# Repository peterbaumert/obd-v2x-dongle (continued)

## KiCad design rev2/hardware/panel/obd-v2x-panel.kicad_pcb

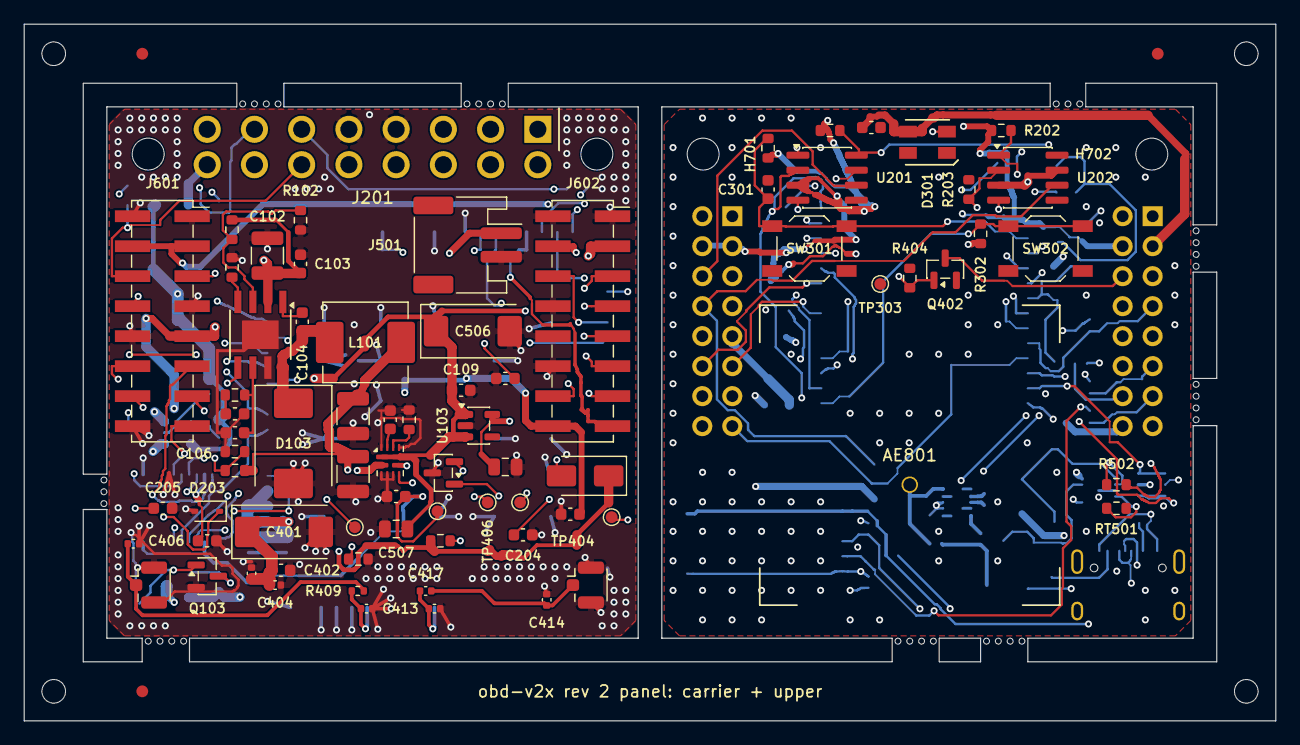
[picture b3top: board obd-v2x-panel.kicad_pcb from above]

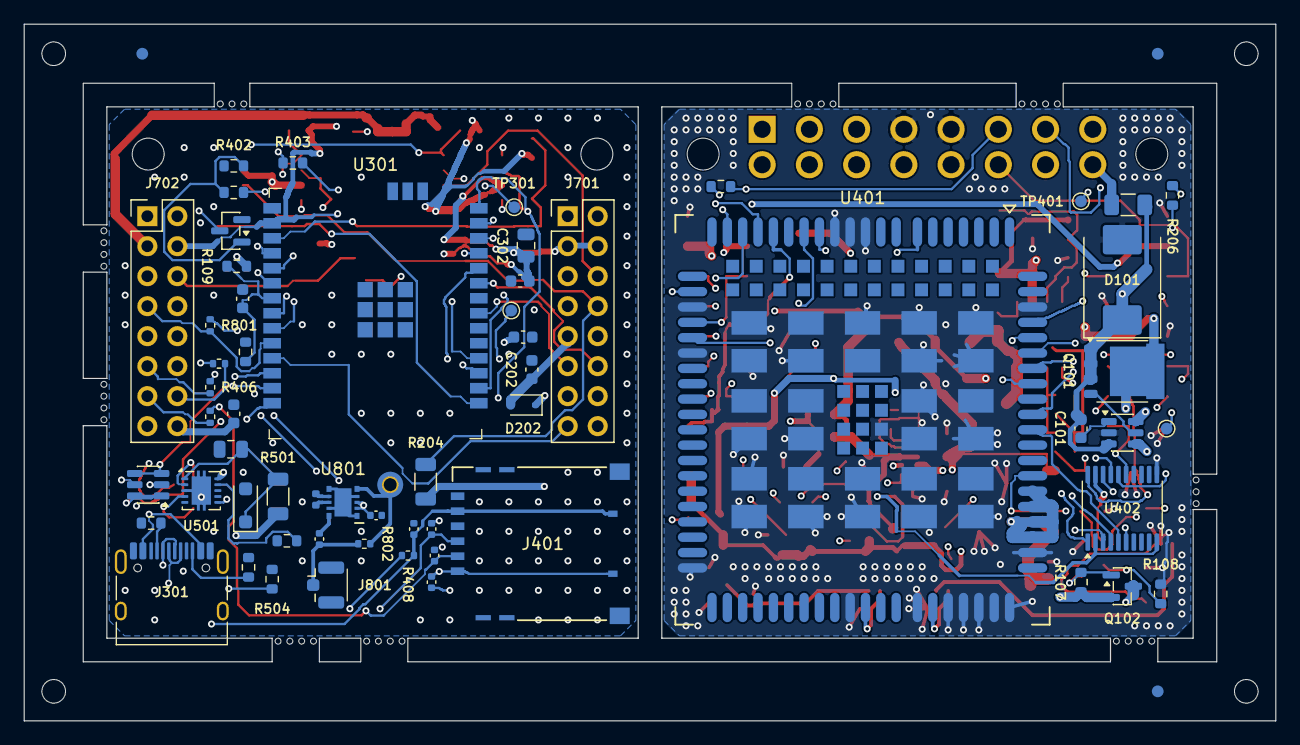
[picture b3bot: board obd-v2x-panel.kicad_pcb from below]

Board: 4 copper layers, 106.0 x 59.0 mm, 182 parts (62 on the bottom side), 112 nets.

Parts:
AE801: CGGBP.25.4.A.02; Antenna_Taoglas_CGGBP.25.4.A.02
C101, C104, C111, C201, C303, C304, C402, C405, C406: 100nF; C_0603_1608Metric
C102: 10uF 50V; C_1210_3225Metric
C103, C202: 100nF 50V; C_0603_1608Metric
C105: 5.6nF; C_0603_1608Metric
C106: 47pF; C_0603_1608Metric
C107, C108: 47uF 10V; C_1210_3225Metric
C109, C301, C502, C505: 1uF; C_0603_1608Metric
C110, C302, C507: 10uF; C_0805_2012Metric
C203: 220pF 50V; C_0603_1608Metric
C204, C205: 560pF 50V; C_0603_1608Metric
C401: 220uF 6.3V; CP_EIA-7343-20_Kemet-V
C403, C407, C408, C409, C417, C801: 33pF; C_0402_1005Metric
C404: 10pF; C_0402_1005Metric
C410, C802: 100nF; C_0402_1005Metric
C411, C412, C413, C414: DNP; C_0402_1005Metric
C501: 1uF 50V; C_0805_2012Metric
C504: 10nF; C_0603_1608Metric
C506: 220uF; CP_EIA-7343-31_Kemet-D
D101: SMCJ33CA; D_SMC
D102: SS14; D_SMA
D103: B560C; D_SMC
D201: NUP2105L; SOT-23
D202: B0540WS; D_SOD-323
D203: PESD1LIN; D_SOD-323
D301: SK6812MINI-HS; LED_SK6812MINI-HS_3.7x3.5mm
D501: SMF24A; D_SOD-123F
F101: 2A slow; Fuse_1206_3216Metric
FID1, FID2, FID3, FID4, FID5, FID6: (no value)
H601, H602, H701, H702: M2.5; MountingHole_2.7mm_M2.5
J201: OBD2_J1962_Plug; OBD2_J1962_Plug_PCB
J301: USB-C; USB_C_Receptacle_HRO_TYPE-C-31-M-12
J401: Micro-SIM; microSIM_Molex_78646-3001
J402: U.FL LTE main; U.FL_Hirose_U.FL-R-SMT-1_Vertical
J403: U.FL GNSS; U.FL_Hirose_U.FL-R-SMT-1_Vertical
J501: Battery 1S; JST_PH_S2B-PH-SM4-TB_1x02-1MP_P2.00mm_Horizontal
J601, J602: Socket 2x8; PinSocket_2x08_P2.54mm_Vertical_SMD
J701, J702: Header 2x8; PinHeader_2x08_P2.54mm_Vertical
J801: U.FL to carrier J403; U.FL_Hirose_U.FL-R-SMT-1_Vertical
L101: 6.8uH 4.5A; L_Sunlord_MWSA0605S
L801: 9.1nH; L_0402_1005Metric
MB1, MB2, MB3, MB4, MB5, MB6, MB7, MB8, MB9, MB10, MB11, MB12, MB13, MB14, MB15, MB16, MB17, MB18, MB19, MB20, MB21, MB22, MB23, MB24, MB25, MB26, MB27, MB28, MB29, MB30, MB31, MB32, MB33, MB34: (no value)
Q101: PSMN7R0-60YS; LFPAK56
Q102: AO3401A; SOT-23
Q103: 2N7002; SOT-23
Q401, Q402: MMBT3904; SOT-23
R101: 470k; R_0603_1608Metric
R102: 120k; R_0603_1608Metric
R103: 162k; R_0603_1608Metric
R104: 37.4k; R_0603_1608Metric
R105, R110, R201, R301, R302: 10k; R_0603_1608Metric
R106: 12k; R_0603_1608Metric
R107, R108, R109, R203: 100k; R_0603_1608Metric
R202, R401, R403: 4.7k; R_0603_1608Metric
R204: 510 0.5W; R_1206_3216Metric
R205, R206: 100R; R_0603_1608Metric
R303, R304: 5.1k; R_0603_1608Metric
R402, R404: 47k; R_0603_1608Metric
R405, R406, R407: 22R; R_0402_1005Metric
R408: 15k; R_0402_1005Metric
R409, R802: 0R; R_0402_1005Metric
R501: 33R 0.5W; R_1206_3216Metric
R502: 4.3k; R_0603_1608Metric
R503: 24k 1%; R_0603_1608Metric
R504, R505: 82k 1%; R_0603_1608Metric
R506: 10k 1%; R_0603_1608Metric
R507: 30.1k 1%; R_0603_1608Metric
R801: 100R; R_0402_1005Metric
RT501: 10k NTC; R_0603_1608Metric
SW301: RESET; SW_SPST_TL3342
SW302: BOOT; SW_SPST_TL3342
TH1, TH2, TH3, TH4: (no value)
TP301: UART0_TX; TestPoint_Pad_D1.0mm
TP302: IO12; TestPoint_Pad_D1.0mm
TP303: GND; TestPoint_Pad_D1.0mm
TP401: LTE_USB_VBUS; TestPoint_Pad_D1.0mm
TP402: LTE_USB_DP; TestPoint_Pad_D1.0mm
TP403: LTE_USB_DM; TestPoint_Pad_D1.0mm
TP404: LTE_USB_BOOT; TestPoint_Pad_D1.0mm
TP405: LTE_DBG_TXD; TestPoint_Pad_D1.0mm
TP406: LTE_DBG_RXD; TestPoint_Pad_D1.0mm
TP407: LTE_1V8; TestPoint_Pad_D1.0mm
U101: LM74700-Q1; SOT-23-6
U102: TPS54360DDA; TI_SO-PowerPAD-8
U103: TLV75733PDBV; SOT-23-5
U201: TCAN334; SOIC-8_3.9x4.9mm_P1.27mm
U202: TJA1021T/20; SOIC-8_3.9x4.9mm_P1.27mm
U301: ESP32-C5-WROOM-1U-N16R8; ESP32-C5-WROOM-1U
U302: USBLC6-2SC6; SOT-23-6
U401: EC200U-EU; Quectel_EC200U
U402: TXS0108EPW; TSSOP-20_4.4x6.5mm_P0.65mm
U501: BQ25171-Q1; Texas_DRC0010J
U502: TPS2121; Texas_VQFN-HR-12_2x2.5mm_P0.5mm
U801: SKY65943-11; Skyworks_SKY65943-11_MCM-10_2.5x2.5mm

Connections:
+3V3: C110.1, C406.1, J601.3, J601.4, J602.4, U103.5, U402.19
/LTE + GNSS (EC200U)/LTE_ANT_GNSS: C413.1, C417.1, U401.47
/LTE + GNSS (EC200U)/LTE_ANT_GNSS_UFL: C414.1, C417.2, J403.1
/LTE + GNSS (EC200U)/LTE_ANT_MAIN: C411.1, R409.1, U401.49
/LTE + GNSS (EC200U)/LTE_CTS_1V8: U401.64, U402.5
/LTE + GNSS (EC200U)/LTE_DBG_RXD: TP406.1, U401.11
/LTE + GNSS (EC200U)/LTE_DBG_TXD: TP405.1, U401.12
/LTE + GNSS (EC200U)/LTE_RTS_1V8: U401.65, U402.4
/LTE + GNSS (EC200U)/LTE_RXD_1V8: U401.68, U402.1
/LTE + GNSS (EC200U)/LTE_STATUS: U401.61, U402.6
/LTE + GNSS (EC200U)/LTE_TXD_1V8: U401.67, U402.3
/LTE + GNSS (EC200U)/LTE_USB_BOOT: TP404.1, U401.115
/LTE + GNSS (EC200U)/LTE_USB_DM: TP403.1, U401.70
/LTE + GNSS (EC200U)/LTE_USB_DP: TP402.1, U401.69
/LTE + GNSS (EC200U)/LTE_USB_VBUS: TP401.1, U401.71
/Power/BUCK_COMP: C106.1, R106.1, U102.6
/Power/BUCK_EN: R101.2, R102.1, U102.3
/Power/BUCK_FB: R104.2, R105.1, U102.5
/Power/LTE_PWR_ON_N: Q102.1, Q103.3, R107.2
/Power/VBAT_F: C101.2, D101.1, F101.2, Q101.1, Q101.2, Q101.3, U101.3, U101.6
CANH: D201.1, J201.6, J601.5, R205.1
CANL: D201.2, J201.14, J601.6, R206.1
GND: C102.2, C103.2, C105.2, C106.2, C107.2, C108.2, C109.2, C110.2, C203.2, C204.2, C205.2, C401.2, C402.2, C403.2, C404.2, C405.2, C406.2, C411.2, C412.2, C413.2, C414.2, C504.2, C505.2, C506.2, C507.2, D101.2, D103.2, D201.3, D203.2, J201.4, J201.5, J402.2, J403.2, J501.2, J601.1, J601.2, J601.7, J601.10, J601.16, J602.1, J602.2, J602.8, J602.10, J602.12, Q103.2, R102.2, R103.2, R105.2, R108.2, R506.2, R507.2, U101.2, U102.7, U102.9, U103.2, U401.8, U401.9, U401.10, U401.19, U401.22, U401.36, U401.46, U401.48, U401.50, U401.51, U401.52, U401.53, U401.54, U401.56, U401.72, U401.76, U401.85, U401.86, U401.87, U401.88, U401.89, U401.90, U401.91, U401.92, U401.93, U401.94, U401.95, U401.96, U401.97, U401.98, U401.99, U401.100, U401.101, U401.102, U401.103, U401.104, U401.105, U401.106, U401.107, U401.108, U401.109, U401.110, U401.111, U401.112, U402.11, U502.3, U502.4, U502.5, U502.9, U502.12
K_LINE: C203.1, D203.1, J201.7, J601.8
LTE_1V8: C405.1, TP407.1, U401.7, U402.2, U402.10
LTE_PWRKEY: J602.5, U401.21
LTE_PWR_EN: J602.7, Q103.1, R108.1
LTE_RESET_N: J602.6, U401.20
LTE_STATUS_3V3: J601.15, U402.15
LTE_USIM_CLK: J602.11, U401.16
LTE_USIM_DATA: J602.13, U401.15
LTE_USIM_RST: J602.14, U401.17
MCU_CTS_LTE: J601.14, U402.16
MCU_RTS_LTE: J601.13, U402.17
MCU_RX_LTE: J601.12, U402.18
MCU_TX_LTE: J601.11, U402.20
unnamed: C105.1, R106.2
unnamed: C204.1, R205.2
unnamed: C205.1, R206.2
unnamed: C104.2, D103.1, L101.1, U102.8
unnamed: C412.1, J402.1, R409.2
unnamed: Q101.4, U101.5
unnamed: C101.1, U101.1
unnamed: C104.1, U102.1
unnamed: R103.1, U102.4
unnamed: R507.1, U502.10
unnamed: R505.2, R506.1, U502.6
unnamed: C504.1, U502.11
OBD_VBAT: F101.1, J201.16
SIM_VDD: J602.15, U401.14
U.+3V3: C201.1, C302.1, C303.1, J701.3, J701.4, J702.4, R201.1, R202.1, R301.1, R302.1, U201.3, U301.2
U./GNSS patch + front end/GNSS_VCC: C802.1, R801.2, U801.2, U801.3
U./MCU (ESP32-C5, USB)/ESP_BOOT: R302.2, SW302.1, U301.15
U./MCU (ESP32-C5, USB)/IO12: TP302.1, U301.24
U./MCU (ESP32-C5, USB)/LED_DIN: D301.2, U301.18
U./MCU (ESP32-C5, USB)/UART0_TX: TP301.1, U301.25
U./MCU (ESP32-C5, USB)/USB_DN: J301.A7, J301.B7, U301.13, U302.3, U302.4
U./MCU (ESP32-C5, USB)/USB_DP: J301.A6, J301.B6, U301.14, U302.1, U302.6
U./Micro-SIM/SIM_CLK: C408.1, J401.3, R406.2
U./Micro-SIM/SIM_IO: C407.1, J401.7, R405.2
U./Micro-SIM/SIM_RST: C409.1, J401.2, R407.2
U.CANH: J701.5, U201.7
U.CANL: J701.6, U201.6
U.CAN_RX: U201.4, U301.16
U.CAN_STB: R201.2, U201.8, U301.12
U.CAN_TX: U201.1, U301.17
U.GND: C111.2, C201.2, C202.2, C301.2, C302.2, C303.2, C304.2, C407.2, C408.2, C409.2, C410.2, C501.2, C502.2, C802.2, D301.1, D501.2, J301.A1, J301.A12, J301.B1, J301.B12, J301.SH, J401.5, J401.SH, J701.1, J701.2, J701.7, J701.10, J701.16, J702.1, J702.2, J702.8, J702.10, J702.12, J801.2, Q401.2, Q402.2, R110.2, R203.2, R303.2, R304.2, R402.2, R404.2, R502.2, R503.2, R504.2, RT501.2, SW301.2, SW302.2, TP303.1, U201.2, U201.5, U202.5, U301.1, U301.28, U301.29, U301.30, U301.32, U302.2, U501.3, U501.5, U501.11, U801.1, U801.4, U801.6, U801.9, U801.11
U.KL_RX: R202.2, U202.1, U301.6
U.KL_SLP_N: R203.1, U202.2, U301.9
U.KL_TX: U202.4, U301.8
U.K_LINE: J701.8, R204.2, U202.6
U.LTE_PWRKEY: J702.5, Q401.3
U.LTE_PWRKEY_CTL: R401.1, U301.4
U.LTE_PWR_EN: J702.7, R801.1, U301.10
U.LTE_RESET_CTL: R403.1, U301.5
U.LTE_RESET_N: J702.6, Q402.3
U.LTE_STATUS_3V3: J701.15, U301.11
U.LTE_USIM_CLK: J702.11, R406.1
U.LTE_USIM_DATA: J702.13, R405.1, R408.2
U.LTE_USIM_RST: J702.14, R407.1
U.MCU_CTS_LTE: J701.14, U301.26
U.MCU_RTS_LTE: J701.13, U301.27
U.MCU_RX_LTE: J701.12, U301.23
U.MCU_TX_LTE: J701.11, U301.21
U.Net-(AE801-A): AE801.1, R802.1, U801.5
U.Net-(D202-K): D202.1, R204.1
U.Net-(D501-K): C501.1, D501.1, R501.2, U501.1
U.Net-(J301-CC1): J301.A5, R303.1
U.Net-(J301-CC2): J301.B5, R304.1
U.Net-(J801-In): C801.2, J801.1, R802.2
U.Net-(Q401-B): Q401.1, R401.2, R402.1
U.Net-(Q402-B): Q402.1, R403.2, R404.1
U.Net-(U301-EN): C301.1, R301.2, SW301.1, U301.3
U.Net-(U501-CHM_TMR): R504.1, U501.6
U.Net-(U501-ISET): R502.1, U501.2
U.Net-(U501-TS): RT501.1, U501.4
U.Net-(U501-VSET): R503.1, U501.9
U.Net-(U801-AMP_IN): L801.2, U801.8
U.Net-(U801-FILT_OUT): L801.1, U801.7
U.Net-(U801-RF_OUT): C801.1, U801.10
U.SIM_VDD: C410.1, J401.1, J702.15, R408.1
U.VBUS_USB: J301.A4, J301.A9, J301.B4, J301.B9, J702.9, U302.5
U.VCELL: C502.1, J702.16, U501.10
U.VIN_PROT: C202.1, D202.2, J701.9, R109.1, R501.1, U202.3, U202.7
U.VSENSE: C111.1, R109.2, R110.1, U301.7
U.VSYS_3V8: C304.1, D301.3, J702.3
VBAT_LTE: C401.1, C402.1, C403.1, C404.1, Q102.3, U401.57, U401.58, U401.59, U401.60
VBUCK_3V8: C107.1, C108.1, L101.2, R104.1, U502.7
VBUS_USB: D102.2, J602.9
VCELL: C505.1, J501.1, J602.16, U502.2
VIN_PROT: C102.1, C103.1, D102.1, J601.9, Q101.5, R101.1, R505.1, U101.4, U102.2
VSYS_3V8: C109.1, C506.1, C507.1, J602.3, Q102.2, R107.1, U103.1, U103.3, U502.1, U502.8

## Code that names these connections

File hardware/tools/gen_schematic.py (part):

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
    sh.text('Input protection: fuse, TVS, ideal-diode reverse protection', g(5), g(6), 1.5, True)
    F = sh.part('Device:Fuse', 'F101', '2A slow', 'Fuse:Fuse_1206_3216Metric', g(14), y0, 90, fields=H(g(14), y0))
    sh.glabel('OBD_VBAT', F.out(1, 1), 'L', 'input')
    sh.w(F.out(1, 1), F[1])

    xt = g(19)
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    sh.w(C[1], U['VCAP'])
    sh.w(C[2], (xv, y0))
    sh.w(U['EN'], (xv - g(2), U['EN'][1]))
    sh.label('VBAT_F', (xv - g(2), U['EN'][1]), 'L')
    sh.label('VBAT_F', (xt + g(3), y0), 'R')
    # main line, input side
    sh.w(F[2], (xt, y0), (xt + g(3), y0), (xv, y0), (xa, y0), Q['S'])
    sh.rail('VIN_PROT', (xc + g(3), y0))
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    Dv.fields = {'ref': (xu + 2.54, Dv.y - 1.27, 'left'), 'val': (xu + 2.54, Dv.y + 1.27, 'left')}
    sh.w(Dv['K'], (xu, y0))
    sh.w(Dv['A'], (xu, Dv['A'][1] - g(1)), (xu - g(1), Dv['A'][1] - g(1)))
    sh.glabel('VBUS_USB', (xu - g(1), Dv['A'][1] - g(1)), 'L', 'input')

    # input caps
    xc1, xc2 = xu + g(4), xu + g(9)
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    R3.fields = {'ref': (xrt - 2.032, R3.y - 1.27, 'right'), 'val': (xrt - 2.032, R3.y + 1.27, 'right')}
    sh.gnd(R3[2])
    # EN divider (labelled)
    sh.label('BUCK_EN', B['EN'], 'L', stub=1)
    xen = g(62)
    R1 = rv(sh, 'Device:R', 'R101', '470k', R0603, xen, y0 + g(9))
    sh.rail('VIN_PROT', R1[1])
    R2 = rv(sh, 'Device:R', 'R102', '120k', R0603, xen, R1[2][1] + g(2))
    sh.w(R1[2], R2[1])
    sh.label('BUCK_EN', (xen, R1[2][1] + g(1)), 'R', stub=0)
    sh.gnd(R2[2])
    # BOOT cap (horizontal, above) between BOOT and SW
    x1 = B['BOOT'][0] + g(1)
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    Rf2 = rv(sh, 'Device:R', 'R105', '10k', R0603, xf, Rf1[2][1] + g(2))
    sh.w(Rf1[2], Rf2[1])
    sh.gnd(Rf2[2])
    sh.label('BUCK_FB', (xf, Rf1[2][1] + g(1)), 'L', stub=0)
    sh.w((xf, Rf1[2][1] + g(1)), (xf - g(1), Rf1[2][1] + g(1)))
    sh.labels[-1] = ('label', 'BUCK_FB', (xf - g(1), Rf1[2][1] + g(1)), 180, None)
    sh.label('BUCK_FB', B['FB'], 'R', stub=1)
    # output caps
    xo1, xo2 = xf + g(5), xf + g(11)
    cap_to_gnd(sh, 'C107', '47uF 10V', C1210, xo1, yo, 2)
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    sh.w(L[2], (xf, yo), (xo1, yo), (xo2, yo), (xo2 + g(3), yo))
    sh.rail('VBUCK_3V8', (xo2 + g(3), yo))   # -> TPS2121 IN1 (battery sheet); loads are on VSYS_3V8
    # compensation (COMP -> R106 -> C105 -> GND, C106 || to GND), labelled
    sh.label('BUCK_COMP', B['COMP'], 'R', stub=1)
    yc = B['GND'][1] + g(5)
    xcmp = XB - g(2)
    sh.label('BUCK_COMP', (xcmp, yc), 'L')
    sh.w((xcmp, yc), (xcmp + g(6), yc))
    Rc = rv(sh, 'Device:R', 'R106', '12k', R0603, xcmp + g(2), yc)
    Cc = rv(sh, 'Device:C', 'C105', '5.6nF', C0603, xcmp + g(2), Rc[2][1] + g(1))
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    sh.w(Rg[2], (Rg[2][0], gt[1] + (g(1) if gt[1] > ys else -g(1))))
    yg = Rg[2][1] + g(1)
    sh.w(Rg[2], (Rg[2][0], yg), (gt[0], yg), gt) if gt[1] > ys else None
    sh.glabel('LTE_PWR_ON_N', (Rg[2][0], yg), 'L', 'output', stub=2)    # low while the modem is powered
    Qn = sh.part('Transistor_FET:2N7002', 'Q103', '2N7002', SOT23, gt[0] - 2.54, yg + g(2) + 5.08, 0,
                 fields={'ref': (gt[0] + 1.27, yg + g(2) + 3.81, 'left'), 'val': (gt[0] + 1.27, yg + g(2) + 6.35, 'left')})
    sh.w((gt[0], yg), Qn['D'])
    sh.gnd(Qn['S'])
    sh.w(Qn['G'], (Qn['G'][0] - g(4), Qn['G'][1]))
    sh.glabel('LTE_PWR_EN', (Qn['G'][0] - g(4), Qn['G'][1]), 'L', 'input')
    Rpd = rv(sh, 'Device:R', 'R108', '100k', R0603, Qn['G'][0] - g(2), Qn['G'][1])
    sh.gnd(Rpd[2])

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    Cs = rv(sh, 'Device:C', 'C111', '100nF', C0603, xs + g(4), yn)
    sh.w((xs, yn), Cs[1], (xs + g(8), yn))
    sh.gnd(Cs[2])
    sh.glabel('VSENSE', (xs + g(8), yn), 'R', 'output')

    # ---------------- power flags
    yf = g(72)
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            sh.gnd(flg[1])
        elif net == 'VBAT_F':
            sh.w(flg[1], (x, yf + g(1)), (x + g(1), yf + g(1)))
            sh.label('VBAT_F', (x + g(1), yf + g(1)), 'R')
        else:
            sh.w(flg[1], (x, yf + g(1)))
            sh.parts.append(None) if False else None
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    sh.text('OBD-II plug (vehicle side)', g(6), g(18), 1.5, True)
    # battery
    sh.w(J['16'], (g(30), J['16'][1]))
    sh.glabel('OBD_VBAT', (g(30), J['16'][1]), 'R', 'output')
    # grounds
    xg = J['5'][0] + g(2)
    sh.w(J['5'], (xg, J['5'][1]))
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    sh.gnd(U['GND'])
    xr = U['TXD'][0]
    sh.w(U['TXD'], (xr + g(3), U['TXD'][1]))
    sh.glabel('CAN_TX', (xr + g(3), U['TXD'][1]), 'R', 'input')
    sh.w(U['RXD'], (xr + g(3), U['RXD'][1]))
    sh.glabel('CAN_RX', (xr + g(3), U['RXD'][1]), 'R', 'output')
    sh.gnd(U['SHDN'], stub=1, rot=90)
    ys = U['STB'][1]
    R = rv(sh, 'Device:R', 'R201', '10k', R0603, xr + g(12), ys - 7.62)
    sh.rail('+3V3', R[1])
    sh.w(U['STB'], (xr + g(12), ys), (xr + g(15), ys))
    sh.glabel('CAN_STB', (xr + g(15), ys), 'R', 'input')
    decap(sh, 'C201', '100nF', C0603, XU + g(8), U['VCC'][1] - g(6), '+3V3')

    # ---------------- K-Line
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    Rx = rv(sh, 'Device:R', 'R202', '4.7k', R0603, xr + g(6), yrx - 7.62)
    sh.rail('+3V3', Rx[1])
    sh.w(K['RXD'], (xr + g(6), yrx), (xr + g(10), yrx))
    sh.glabel('KL_RX', (xr + g(10), yrx), 'R', 'output')
    sh.w(K['TXD'], (xr + g(10), K['TXD'][1]))
    sh.glabel('KL_TX', (xr + g(10), K['TXD'][1]), 'R', 'input')
    ysl = K['~{SLP}'][1]
    sh.w(K['~{SLP}'], (xr + g(6), ysl), (xr + g(10), ysl))
    sh.glabel('KL_SLP_N', (xr + g(10), ysl), 'R', 'input')
    Rs = rv(sh, 'Device:R', 'R203', '100k', R0603, xr + g(6), ysl + g(2))
    sh.w((xr + g(6), ysl), Rs[1])
    sh.gnd(Rs[2])
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    sh.gnd(bot)
    yn = Rb[2][1] + g(1)
    sh.w((xb, yn), (xb - g(3), yn))
    sh.label('ESP_BOOT', (xb - g(3), yn), 'L')
    # LED
    Dl = sh.part('obd-v2x:SK6812MINI-HS', 'D301', 'SK6812MINI-HS', 'obd-v2x:LED_SK6812MINI-HS_3.7x3.5mm', g(98), g(36), 0)
    Dl.fields = {'ref': (g(98) + g(4), g(35), 'left'), 'val': (g(98) + g(4), g(37), 'left')}
    sh.rail('VSYS_3V8', Dl['VDD'])
    sh.gnd(Dl['GND'])
    sh.w(Dl['DIN'], Dl.out('DIN', 2))
    sh.label('LED_DIN', Dl.out('DIN', 2), 'L')
    sh.nc(Dl, 'DOUT')
    decap(sh, 'C304', '100nF', C0603, g(106), g(30), 'VSYS_3V8')

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    J.fields = {'ref': (Jx - g(6), Jy - g(10), 'left'), 'val': (Jx - g(6), Jy - g(9), 'left')}
    xr = J['A4'][0]
    sh.w(J['A4'], (xr + g(8), J['A4'][1]))
    sh.glabel('VBUS_USB', (xr + g(8), J['A4'][1]), 'R', 'output')
    Rc1 = rh(sh, 'Device:R', 'R303', '5.1k', R0603, xr + g(2), J['A5'][1])
    sh.w(J['A5'], Rc1[1])
    sh.gnd(Rc1[2], rot=90)
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    xd = xr + g(2)
    sh.w(J['A7'], (xd, J['A7'][1]), (xd, J['B7'][1]), J['B7'])
    sh.w((xd, J['A7'][1]), (xd + g(3), J['A7'][1]))
    sh.label('USB_DN', (xd + g(3), J['A7'][1]), 'R')
    sh.w(J['A6'], (xd, J['A6'][1]), (xd, J['B6'][1]), J['B6'])
    sh.w((xd, J['B6'][1]), (xd + g(3), J['B6'][1]))
    sh.label('USB_DP', (xd + g(3), J['B6'][1]), 'R')
    sh.nc(J, 'A8')
    sh.nc(J, 'B8')
    sh.w(J['SH'], J['A1'])
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    # ESD
    E = sh.part('Power_Protection:USBLC6-2SC6', 'U302', 'USBLC6-2SC6', 'Package_TO_SOT_SMD:SOT-23-6', g(44), g(62), 0)
    E.fields = {'ref': (g(44) + g(2), g(62) - g(3), 'left'), 'val': (g(44) + g(2), g(62) + g(4), 'left')}
    for pin, net, side in (('1', 'USB_DP', 'L'), ('3', 'USB_DN', 'L'), ('6', 'USB_DP', 'R'), ('4', 'USB_DN', 'R')):
        sh.w(E[pin], E.out(pin, 2))
        sh.label(net, E.out(pin, 2), side)
    sh.w(E['VBUS'], E.out('VBUS', 1))
    sh.glabel('VBUS_USB', E.out('VBUS', 1), 'U', 'input')
    sh.gnd(E['GND'])
    # test points
    sh.text('Test pads: UART0 TX, SIM_SEL (IO12, was RXD0)', g(64), g(56), 1.5, True)
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    sh.gnd((U['10'][0] + g(2), U['10'][1]), rot=90)
    sh.gnd(U['8'])
    # VBAT decoupling
    sh.text('VBAT_LTE bulk/decoupling (close to pins 57-60)', g(3), g(55), 1.27, True)
    decap(sh, 'C401', '220uF 6.3V', 'Capacitor_Tantalum_SMD:CP_EIA-7343-31_Kemet-D', g(5), g(58), 'VBAT_LTE', lib='Device:C_Polarized')
    decap(sh, 'C402', '100nF', C0603, g(13), g(58), 'VBAT_LTE')
    decap(sh, 'C403', '33pF', C0402, g(19), g(58), 'VBAT_LTE')
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    sh.w(S['VCC'], (xj - g(2), S['VCC'][1]))
    sh.label('SIM1_VDD', (xj - g(2), S['VCC'][1]), 'L')
    xR = xj - g(12)
    for pin, net, rref, src, dy in (('RST', 'SIM_RST', 'R407', 'SIM1_RST', -2), ('CLK', 'SIM_CLK', 'R406', 'SIM1_CLK', 0),
                                    ('I/O', 'SIM_IO', 'R405', 'SIM1_DAT', 0)):
        y = S[pin][1]
        yr = y + g(dy)
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    Rpu = rv(sh, 'Device:R', 'R408', '15k', R0402, g(106), g(55))
    Rpu.fields = {'ref': (g(106) + g(1), Rpu.y - 1.27, 'left'), 'val': (g(106) + g(1), Rpu.y + 1.27, 'left')}
    sh.w(Rpu[1], (g(106), g(54)))
    sh.label('SIM_VDD', (g(106), g(54)), 'U')
    sh.w(Rpu[2], (g(106), Rpu[2][1] + g(1)), (g(108), Rpu[2][1] + g(1)))
    sh.label('LTE_USIM_DATA', (g(108), Rpu[2][1] + g(1)), 'R')

    # antennas
    sh.text('Antennas (pi-match, shunt caps DNP until tuned)', g(22), g(64), 1.27, True)
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        sh.w((xr2, y), Jc['1'])
        sh.gnd(Jc['2'])
        if j == 'J403':
            sh.label('LTE_ANT_GNSS_UFL', (xr2 + g(1), y), 'U', stub=2)

    # GNSS active-antenna bias: 3.3 V while the modem is powered, through a latch-off current-limited switch
    # (100-137 mA) and an RF choke onto the U.FL side. Passive antennas: harmless if DC-open; a DC-shorted one
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
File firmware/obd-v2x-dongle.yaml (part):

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modem:
  id: lte
  model: GENERIC
  tx_pin: GPIO23              # IO23 (pin 21) MCU_TX_LTE -> modem RXD
  rx_pin: GPIO24              # IO24 (pin 23) MCU_RX_LTE <- modem TXD
  rts_pin: GPIO26             # IO26 (pin 27) MCU_RTS_LTE -> modem RTS
  cts_pin: GPIO25             # IO25 (pin 26) MCU_CTS_LTE <- modem CTS
  # 921600 instead of the default 115200 (~11 kB/s, too slow for busy roads): the component starts at 115200,
  # switches the EC200U with AT+IPR and remembers the rate. RTS/CTS flow control; the TXS0108E handles this easily.
  baud_rate: 921600
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# components/obd2 (ESPHome's esp32_can does not link on the ESP32-C5). Only active while the engine runs.
obd2:
  id: obd
  tx_pin: GPIO4               # IO4 (pin 17) CAN_TX -> TCAN334
  rx_pin: GPIO5               # IO5 (pin 16) CAN_RX <- TCAN334
  standby_pin: GPIO10         # IO10 (pin 12) TCAN334 STB, high = standby
  bit_rate: 500000
  poll_interval: 250ms        # one request per 250 ms, round robin (speed/RPM twice per round)
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
# ---------------------------------------------------------------- sensors
sensor:
  - platform: adc             # IO1 (pin 7) VSENSE = VIN_PROT / 11 (R109 100k / R110 10k)
    id: car_battery
    name: "Car battery"
    pin: GPIO1
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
